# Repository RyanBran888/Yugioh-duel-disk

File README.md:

# why i made project
i like yugioh, so i build thing from yugioh :3
# what does the project do?
it is basically a calculator that can do 2 calculation screens at once and it has special buttons that would be useful for yugioh
# how doe sit allll fit together
i code the stuff that i put on the pcb

# BOM
16 buttons, price $8 (i can only find in pack of 200), link https://www.amazon.com/Hilitchi-200-Pcs-Tactile-Momentary-Assortment/dp/B071KX71SV 
1 swtich, price $9, https://www.digikey.com/en/products/detail/nkk-switches/GW12LJPCF/1014808
2 screens, price $15 (can only find pack of 15) https://yanlania.com/products/copy-of-0-39-inches-5-digital-7-segment-led-display-red-illuminated-ultra-bright-x10pcs?srsltid=AfmBOoo-E4cp0fLrsGiIyAsbQR7TzCg4ztavmSq28jkVQcu-OPAeRpD1
2 resistors, price free i have a lot of them already
16 diodes, $0.17 each, https://juriedengineering.com/products/1n4148-do-35-switching-signal-diode-new?utm_source=chatgpt.com
pico, $5, https://www.amazon.com/Raspberry-Pi-Pico/dp/B09KVB8LVR/ref=asc_df_B09KVB8LVR?mcid=b3d7090e0aaf3fac91ccf1579d413aef&hvocijid=11375418671374882239-B09KVB8LVR-&hvexpln=73&tag=hyprod-20&linkCode=df0&hvadid=721245378154&hvpos=&hvnetw=g&hvrand=11375418671374882239&hvpone=&hvptwo=&hvqmt=&hvdev=c&hvdvcmdl=&hvlocint=&hvlocphy=9012421&hvtargid=pla-2281435177858&psc=1 
MCP23017_SO i/o expander, $1.70, https://www.digikey.com/en/products/detail/microchip-technology/MCP23017-E-SS/894273?utm_source=chatgpt.com
pcb, $32.15, jlcpcb

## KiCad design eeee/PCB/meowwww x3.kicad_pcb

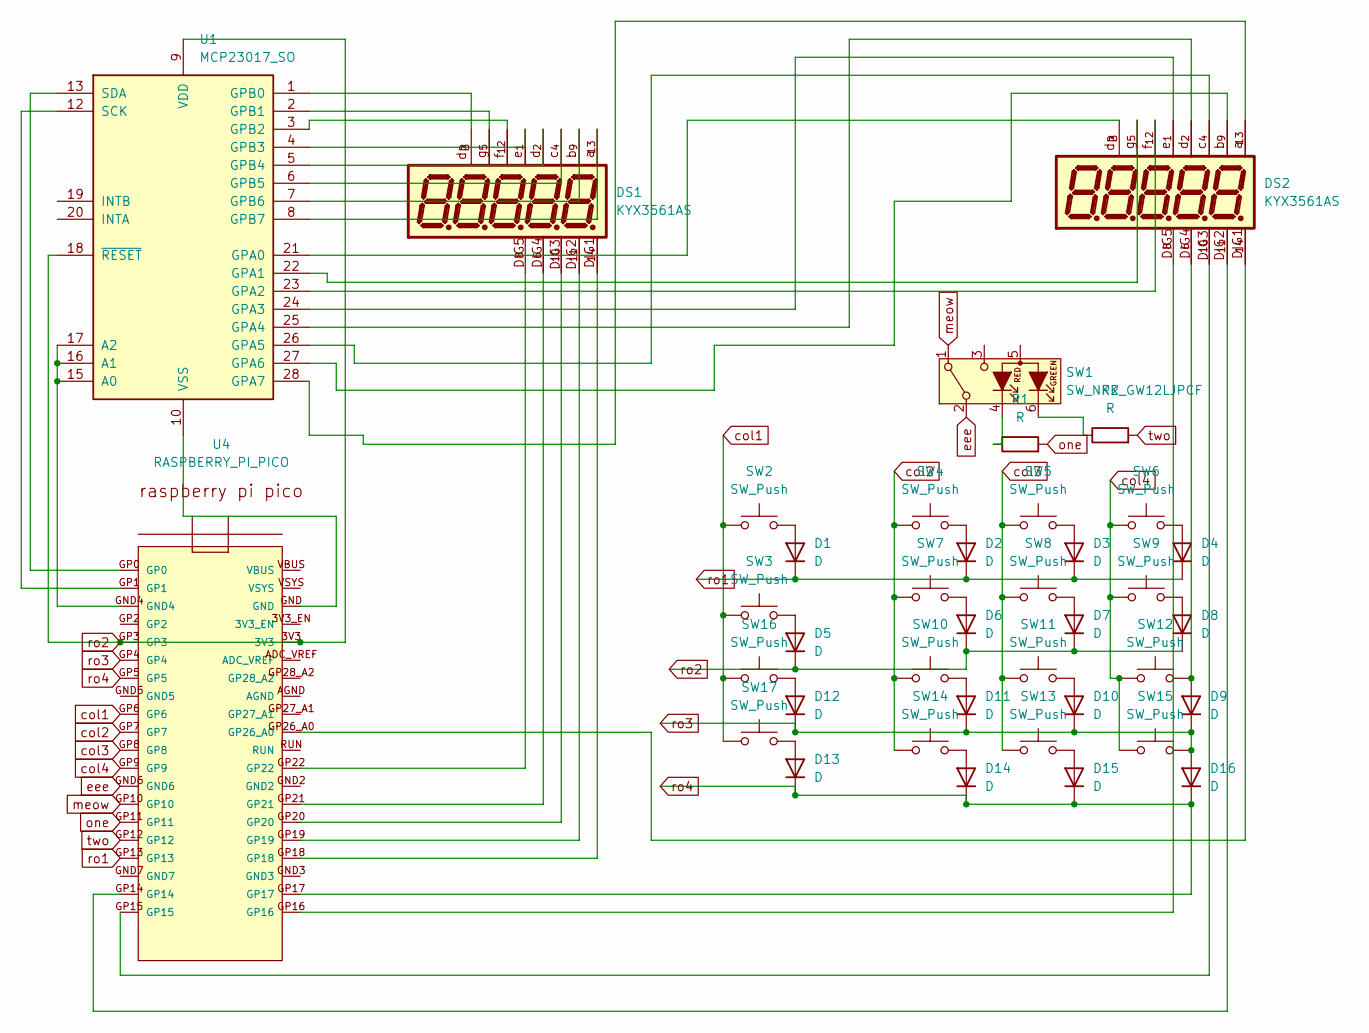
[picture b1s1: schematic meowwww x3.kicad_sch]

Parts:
D1, D2, D3, D4, D5, D6, D7, D8, D9, D10, D11, D12, D13, D14, D15, D16: D; D_DO-35_SOD27_P3.81mm_Vertical_KathodeUp
DS1, DS2: KYX3561AS; DISPLAY_KYX3561AS
R1, R2: R; R_Axial_DIN0207_L6.3mm_D2.5mm_P7.62mm_Horizontal
SW1: SW_NKK_GW12LJPCF; SW_NKK_GW12LJP
SW2, SW3, SW4, SW5, SW6, SW7, SW8, SW9, SW10, SW11, SW12, SW13, SW14, SW15, SW16, SW17: SW_Push; SW_PUSH_6mm
U1: MCP23017_SO; SOIC-28W_7.5x17.9mm_P1.27mm
U4: RASPBERRY_PI_PICO

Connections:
unnamed: D1.2 (A), SW2.2
unnamed: D2.2 (A), SW4.2
unnamed: D3.2 (A), SW5.2
unnamed: D4.2 (A), SW6.2
unnamed: D5.2 (A), SW3.2
unnamed: D6.2 (A), SW7.2
unnamed: D7.2 (A), SW8.2
unnamed: D8.2 (A), SW9.2
unnamed: D9.2 (A), DS2.6, SW12.2
unnamed: D10.2 (A), SW11.2
unnamed: D11.2 (A), SW10.2
unnamed: D12.2 (A), SW16.2
unnamed: D13.2 (A), SW17.2
unnamed: D14.2 (A), SW14.2
unnamed: D15.2 (A), SW13.2
unnamed: DS1.6, U4.GP21
unnamed: DS1.8, U4.GP22
unnamed: DS1.10, U4.GP20
unnamed: DS1.11, U4.GP19
unnamed: DS1.14, U4.GP18
unnamed: DS2.8, U4.GP16
unnamed: DS2.10, U4.GP15
unnamed: DS2.11, U4.GP14
unnamed: DS2.14, U4.GP26_A0
unnamed: R2.1, SW1.6 (KG)
unnamed: R1.1, SW1.4 (KR)
unnamed: U1.15 (A0), U1.16 (A1), U1.17 (A2), U4.GND4
unnamed: DS2.3, U1.21 (GPA0)
unnamed: DS2.5, U1.22 (GPA1)
unnamed: DS2.12, U1.23 (GPA2)
unnamed: DS2.1, U1.24 (GPA3)
unnamed: DS2.2, U1.25 (GPA4)
unnamed: DS2.4, U1.26 (GPA5)
unnamed: DS2.9, U1.27 (GPA6)
unnamed: DS2.13, U1.28 (GPA7)
unnamed: DS1.3, U1.1 (GPB0)
unnamed: DS1.5, U1.2 (GPB1)
unnamed: DS1.12, U1.3 (GPB2)
unnamed: DS1.1, U1.4 (GPB3)
unnamed: DS1.2, U1.5 (GPB4)
unnamed: DS1.4, U1.6 (GPB5)
unnamed: DS1.9, U1.7 (GPB6)
unnamed: DS1.13, U1.8 (GPB7)
unnamed: U1.12 (SCK), U4.GP1
unnamed: U1.13 (SDA), U4.GP0
unnamed: U1.10 (VSS), U4.GND
col1: SW2.1, SW3.1, SW16.1, SW17.1, U4.GP6
col2: SW4.1, SW7.1, SW10.1, SW14.1, U4.GP7
col3: SW5.1, SW8.1, SW11.1, SW13.1, U4.GP8
col4: SW6.1, SW9.1, SW12.1, SW15.1, U4.GP9
eee: SW1.2 (B), U4.GND6
meow: SW1.1 (A), U4.GP10
one: R1.2, U4.GP11
ro1: D1.1 (K), D2.1 (K), D3.1 (K), D4.1 (K), U4.GP13
ro2: D5.1 (K), D6.1 (K), D7.1 (K), D8.1 (K), U1.9 (VDD), U1.18 (~RESET), U4.3V3, U4.GP3
ro3: D9.1 (K), D10.1 (K), D11.1 (K), D12.1 (K), D16.2 (A), SW15.2, U4.GP4
ro4: D13.1 (K), D14.1 (K), D15.1 (K), D16.1 (K), U4.GP5, U4.GP17
two: R2.2, U4.GP12

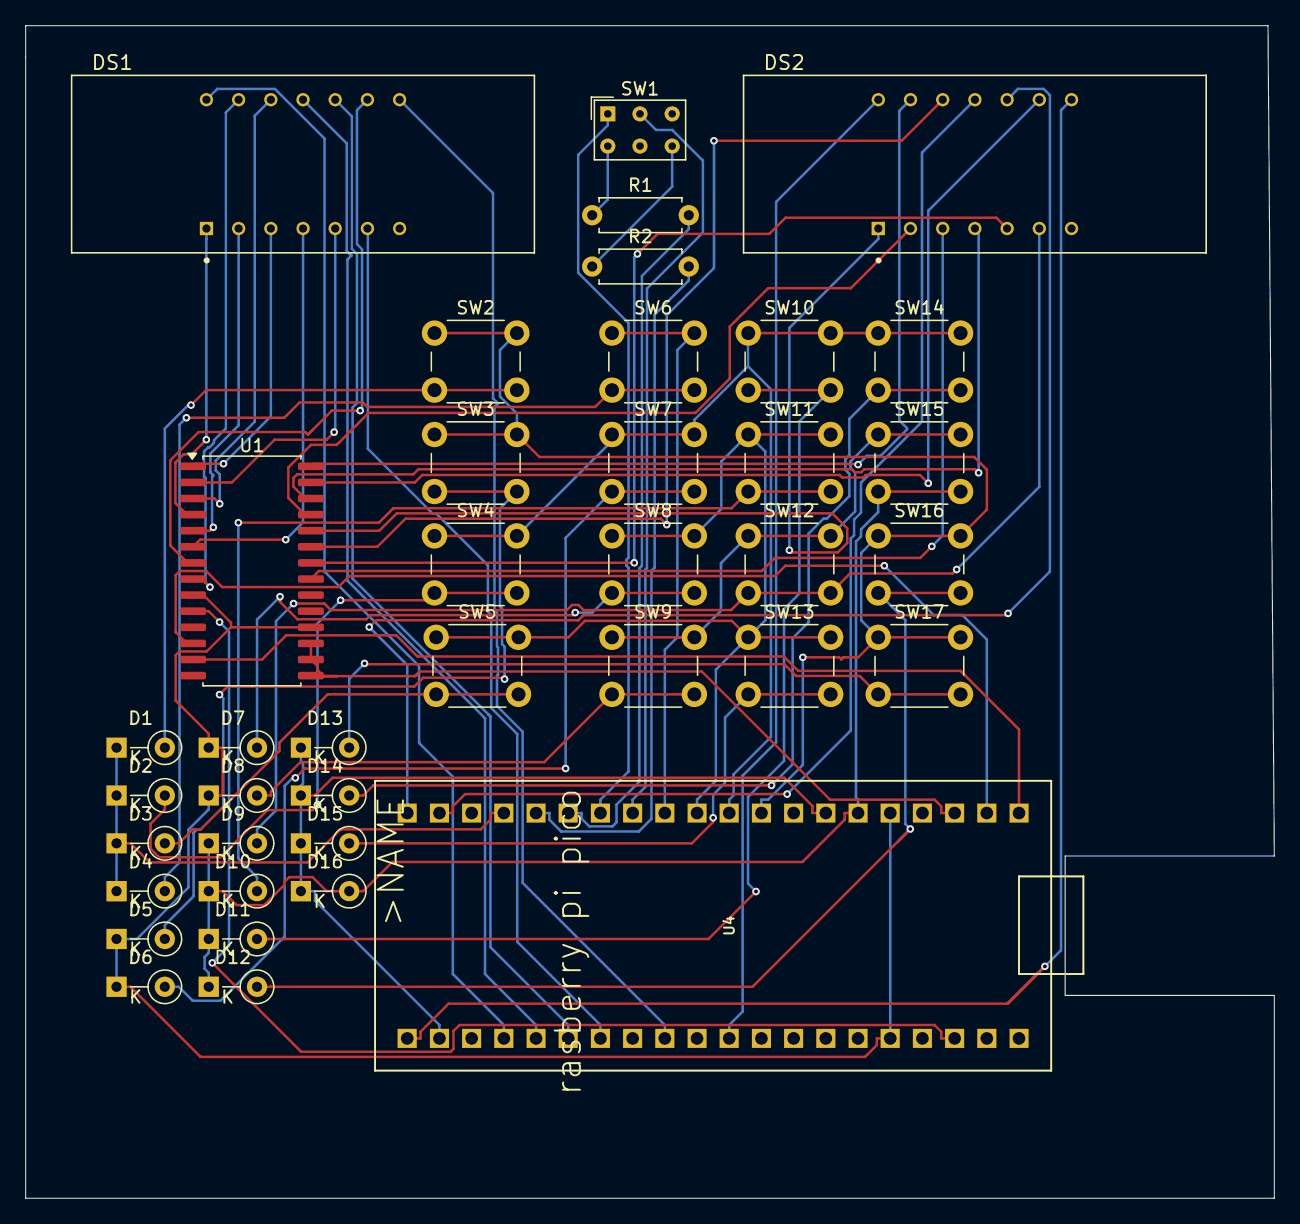
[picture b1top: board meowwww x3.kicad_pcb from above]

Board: 2 copper layers, 98.5 x 92.5 mm, 39 parts (0 on the bottom side), 58 nets.
